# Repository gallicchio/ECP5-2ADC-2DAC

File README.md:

# ECP5-2ADC-2DAC

**Completely Open: Schematic, PCB, FPGA, Verilog, RISC-V processor, Linux, Ethernet, 2 ADCs, 2 DACs**

**Board A at work, 2026-11-18**, measuring the passive circuits on the AMOD-P board (left).
- **Cabling:** DAC 1 OUT drives a circuit and ADC A IN reads it back, over the SMA cables. The clock loops from CLK OUT back to CLK IN.
- **LEDs:** all eight red rail LEDs are lit, and so are a white user LED, the RGB LED (blue) and the Ethernet link LED (green).
- **Results:** every measurement so far is in [`bringup/BRINGUP_LOG.md`](bringup/BRINGUP_LOG.md).

> [!WARNING]
> ## Rev A mostly works, but only after soldering work. Wait for rev B.
> **Do not order this board yet.** Rev A's programming port is dead until two things are changed with a
> soldering iron and a cut cable, and it has other faults listed below. Rev B will fix them.

<p>  </p>

Rev A as delivered. The back is [here](photos/20261116_084538.jpg). The same board as drawn in KiCad:

<p>  </p>

Click any image to open it at full size.

## What it is for

A better version of the [Icepi Zero DAC/ADC tutorials](https://github.com/gallicchio/icepi-zero-dac-adc), on a
board made for them:

- **Two synchronized channels** in and two out, for things like I/Q. One dual ADC, one dual DAC.
- **Gigabit Ethernet**, so samples stream to a laptop at hundreds of megabits a second.
- **Nothing closed** between the laptop and the converters' pins. No vendor tool, no licence, no account.

| | |
|---|---|
| FPGA | Lattice ECP5, LFE5U-25F: 24k LUTs |
| Inputs | 2 x 12 bits, 65 MS/s (AD9238), DC-coupled, ±1 V, gain 1, 10 or 100, 50 Ω or high impedance |
| Outputs | 2 x 14 bits, 125 MS/s (AD9767), DC-coupled, ±1 V into 50 Ω |
| Clocks | 25 MHz TCXO, Si5351, clock in and clock out on SMA |
| Memory | 32 MB SDRAM, 16 MB flash, microSD |
| Ports | gigabit Ethernet, USB-C (JTAG and serial), a second USB-C, mini-HDMI, two Pmods |
| Extras | an LED driver and a photodiode receiver, for optics; a noise source |
| Board | 158 x 119 mm, 6 layers, one 5 V USB-C, about 3 W |

## Status of rev A

Two boards were assembled. One has been powered, on 2026-11-16 and 17.

| | status | detail |
|---|---|---|
| Power: every rail from one USB-C | **works** | |
| USB port for programming and serial | **dead as built** | works after the two changes below |
| Boot from flash | **works** | |
| 32 MB SDRAM | **works** | with its clock inverted in the FPGA; no error over the whole memory at 62.5 MHz |
| Clocks | **work** | the Si5351 to 225 MHz |
| ADC, both channels | **works** | clean to 87.5 MS/s; about 10.5 effective bits on small signals; large signals distort above about 2 MHz |
| DAC, both channels | **works** | clean at 187.5 MS/s |
| Gigabit Ethernet | **works** | both ADCs at 25 MS/s into GNU Radio: 858 Mbit/s, no packet lost |
| RISC-V Linux | **boots** | LiteX with a VexRiscv core at 50 MHz, Linux 6.12, loaded over the network |
| Second USB-C, the FPGA's own | does not work | cause not found |
| microSD | does not answer | not diagnosed |
| Pmod sockets | wrong | mirrored against the Pmod standard |
| HDMI, LED driver, photodiode receiver | not tested yet | |
| The second assembled board | not powered yet | |

The powered board's ADC stage was then damaged by a test lead that shorted on it. It still works; signals near
full scale are compressed. The record: [`bringup/STATUS.md`](bringup/STATUS.md),
[`bringup/BRINGUP_LOG.md`](bringup/BRINGUP_LOG.md).

### What rev A needs before it works

| fault | change |
|---|---|
| Two supply pins of the USB chip (FT2232H) get 1.8 V. They need 3.3 V. | Remove ferrite bead FB6241. Solder a wire from +3V3 to its **left pad only**. |
| The USB data lines D+ and D- are swapped at the chip. | Use a USB cable with those two wires crossed. |

Either fault alone keeps the board off the PC. A wire across both pads of FB6241 puts 3.3 V on the chip's 1.8 V
core. Every fault and its fix for rev B: [`bringup/REVB.md`](bringup/REVB.md).

## What "completely open" means here

| layer | what | built with |
|---|---|---|
| Schematic, PCB | a KiCad 10 project, generated by Python in `gen/` and `pcb/` | KiCad |
| FPGA | Lattice ECP5 | Yosys, nextpnr, Project Trellis, openFPGALoader |
| Verilog | the bring-up designs in [`gateware/bringup/`](gateware/bringup/README.md) | |
| RISC-V processor | VexRiscv in a LiteX system; the board's platform file is [`gateware/litex/`](gateware/litex/) | LiteX |
| Linux | 6.12, with a driver for the converters | Buildroot |
| Ethernet | RTL8211F PHY; UDP in Verilog, or LiteEth | |

The chips themselves are ordinary closed silicon with public data sheets.

Against a Red Pitaya STEMlab 125-14:

| | Red Pitaya | this board |
|---|---|---|
| Inputs | 2 x 14 bits, 125 MS/s | 2 x 12 bits, 65 MS/s |
| Outputs | 2 x 14 bits, 125 MS/s | 2 x 14 bits, 125 MS/s |
| FPGA and its tools | Xilinx Zynq: Vivado | Lattice ECP5: Yosys and nextpnr |
| Processor | ARM cores in the Zynq | a RISC-V core you can read, in the FPGA |
| Memory | 512 MB | 32 MB |

Fewer bits in and a slower processor; nothing you cannot open.

## What is here

| path | what |
|---|---|
| `*.kicad_sch`, `ECP5-2ADC-2DAC.kicad_pcb` | the KiCad 10 project; the schematic as [PDF](docs/images/ECP5-2ADC-2DAC_schematic.pdf) |
| [`mfg/release/`](mfg/release/) | what was uploaded to JLCPCB: Gerbers, BOM, placement |
| [`gateware/`](gateware/bringup/README.md) | the pin constraints, the bring-up Verilog and its bitstreams, the LiteX platform file |
| [`bringup/`](bringup/README.md) | the bench programs, the log of every measurement, the list for rev B |
| `gen/`, `pcb/`, `mfg/`, `tools/`, `sim/` | the scripts that generate and check the design (`python3 build.py`) |
| [`docs/DESIGN.md`](docs/DESIGN.md) | the design and its reasons, build by build |
| [`design_review/`](design_review/README.md) | six reviews before the order, and [what was done about them](DESIGN_REVIEW_RESPONSE.md) |
| [`photos/`](photos/README.md) | the board as delivered |

## How it was made

Jason Gallicchio designed this with Claude (Anthropic's Fable 5.1 and Opus 5.5, in Claude Code).

| | dates | days |
|---|---|---|
| Design, to the order at JLCPCB | 2026-10-01 to 2026-10-09 | 9 |
| Boards delivered | 2026-11-05 | |
| Bring-up and debugging so far | 2026-11-16 to 2026-11-17 | 2 |

Every prompt and every response is kept: [`CLAUDE_CODE_CHAT.md`](CLAUDE_CODE_CHAT.md).

The board grew up in a private repository of the research group. Its commits are here; vendor datasheets are
not. Commit hashes quoted in the documents are the old ones: [`docs/COMMIT_MAP.tsv`](docs/COMMIT_MAP.tsv).

## Licence

Hardware under CERN-OHL-P-2.0, software under MIT: [`LICENSE`](LICENSE).

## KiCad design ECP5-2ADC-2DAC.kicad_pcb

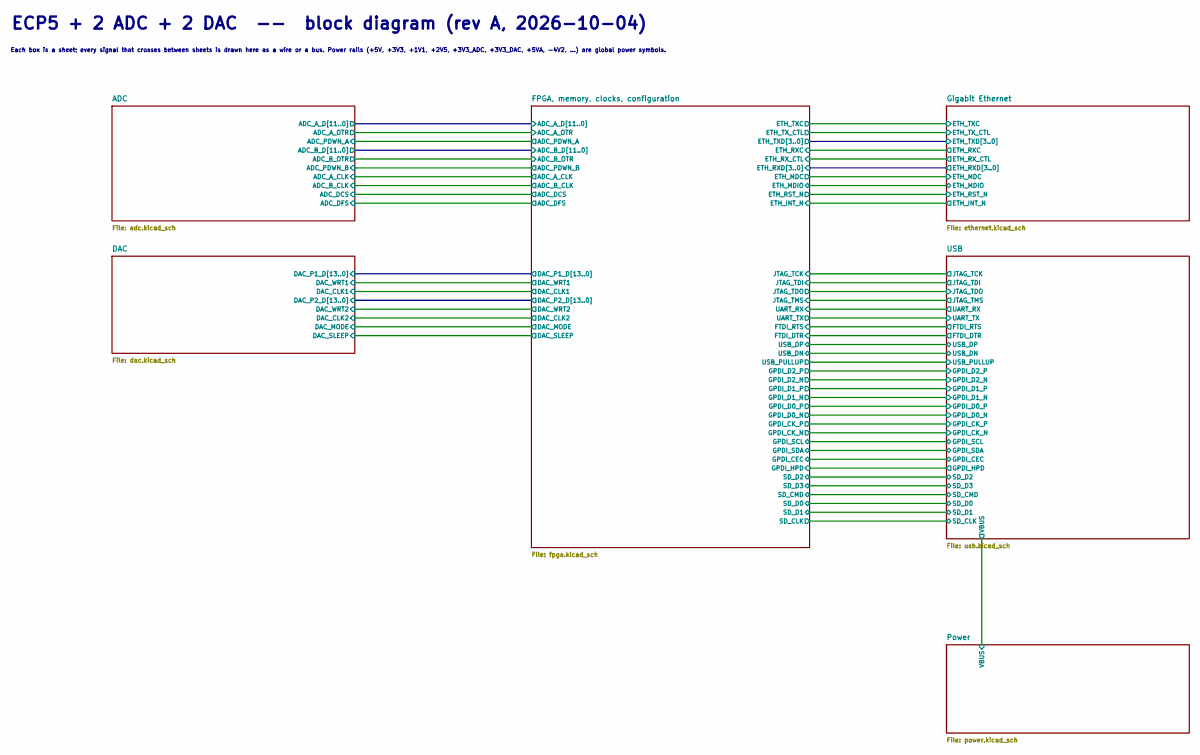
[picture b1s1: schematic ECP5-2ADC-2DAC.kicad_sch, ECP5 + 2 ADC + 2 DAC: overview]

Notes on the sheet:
ECP5 + 2 ADC + 2 DAC -- block diagram (rev A, 2026-10-04)
Each box is a sheet; every signal that crosses between sheets is drawn here as a wire or a bus. Power rails (+5V, +3V3, +1V1, +2V5, +3V3_ADC, +3V3_DAC, +5VA, -4V2, ...) are global power symbols.

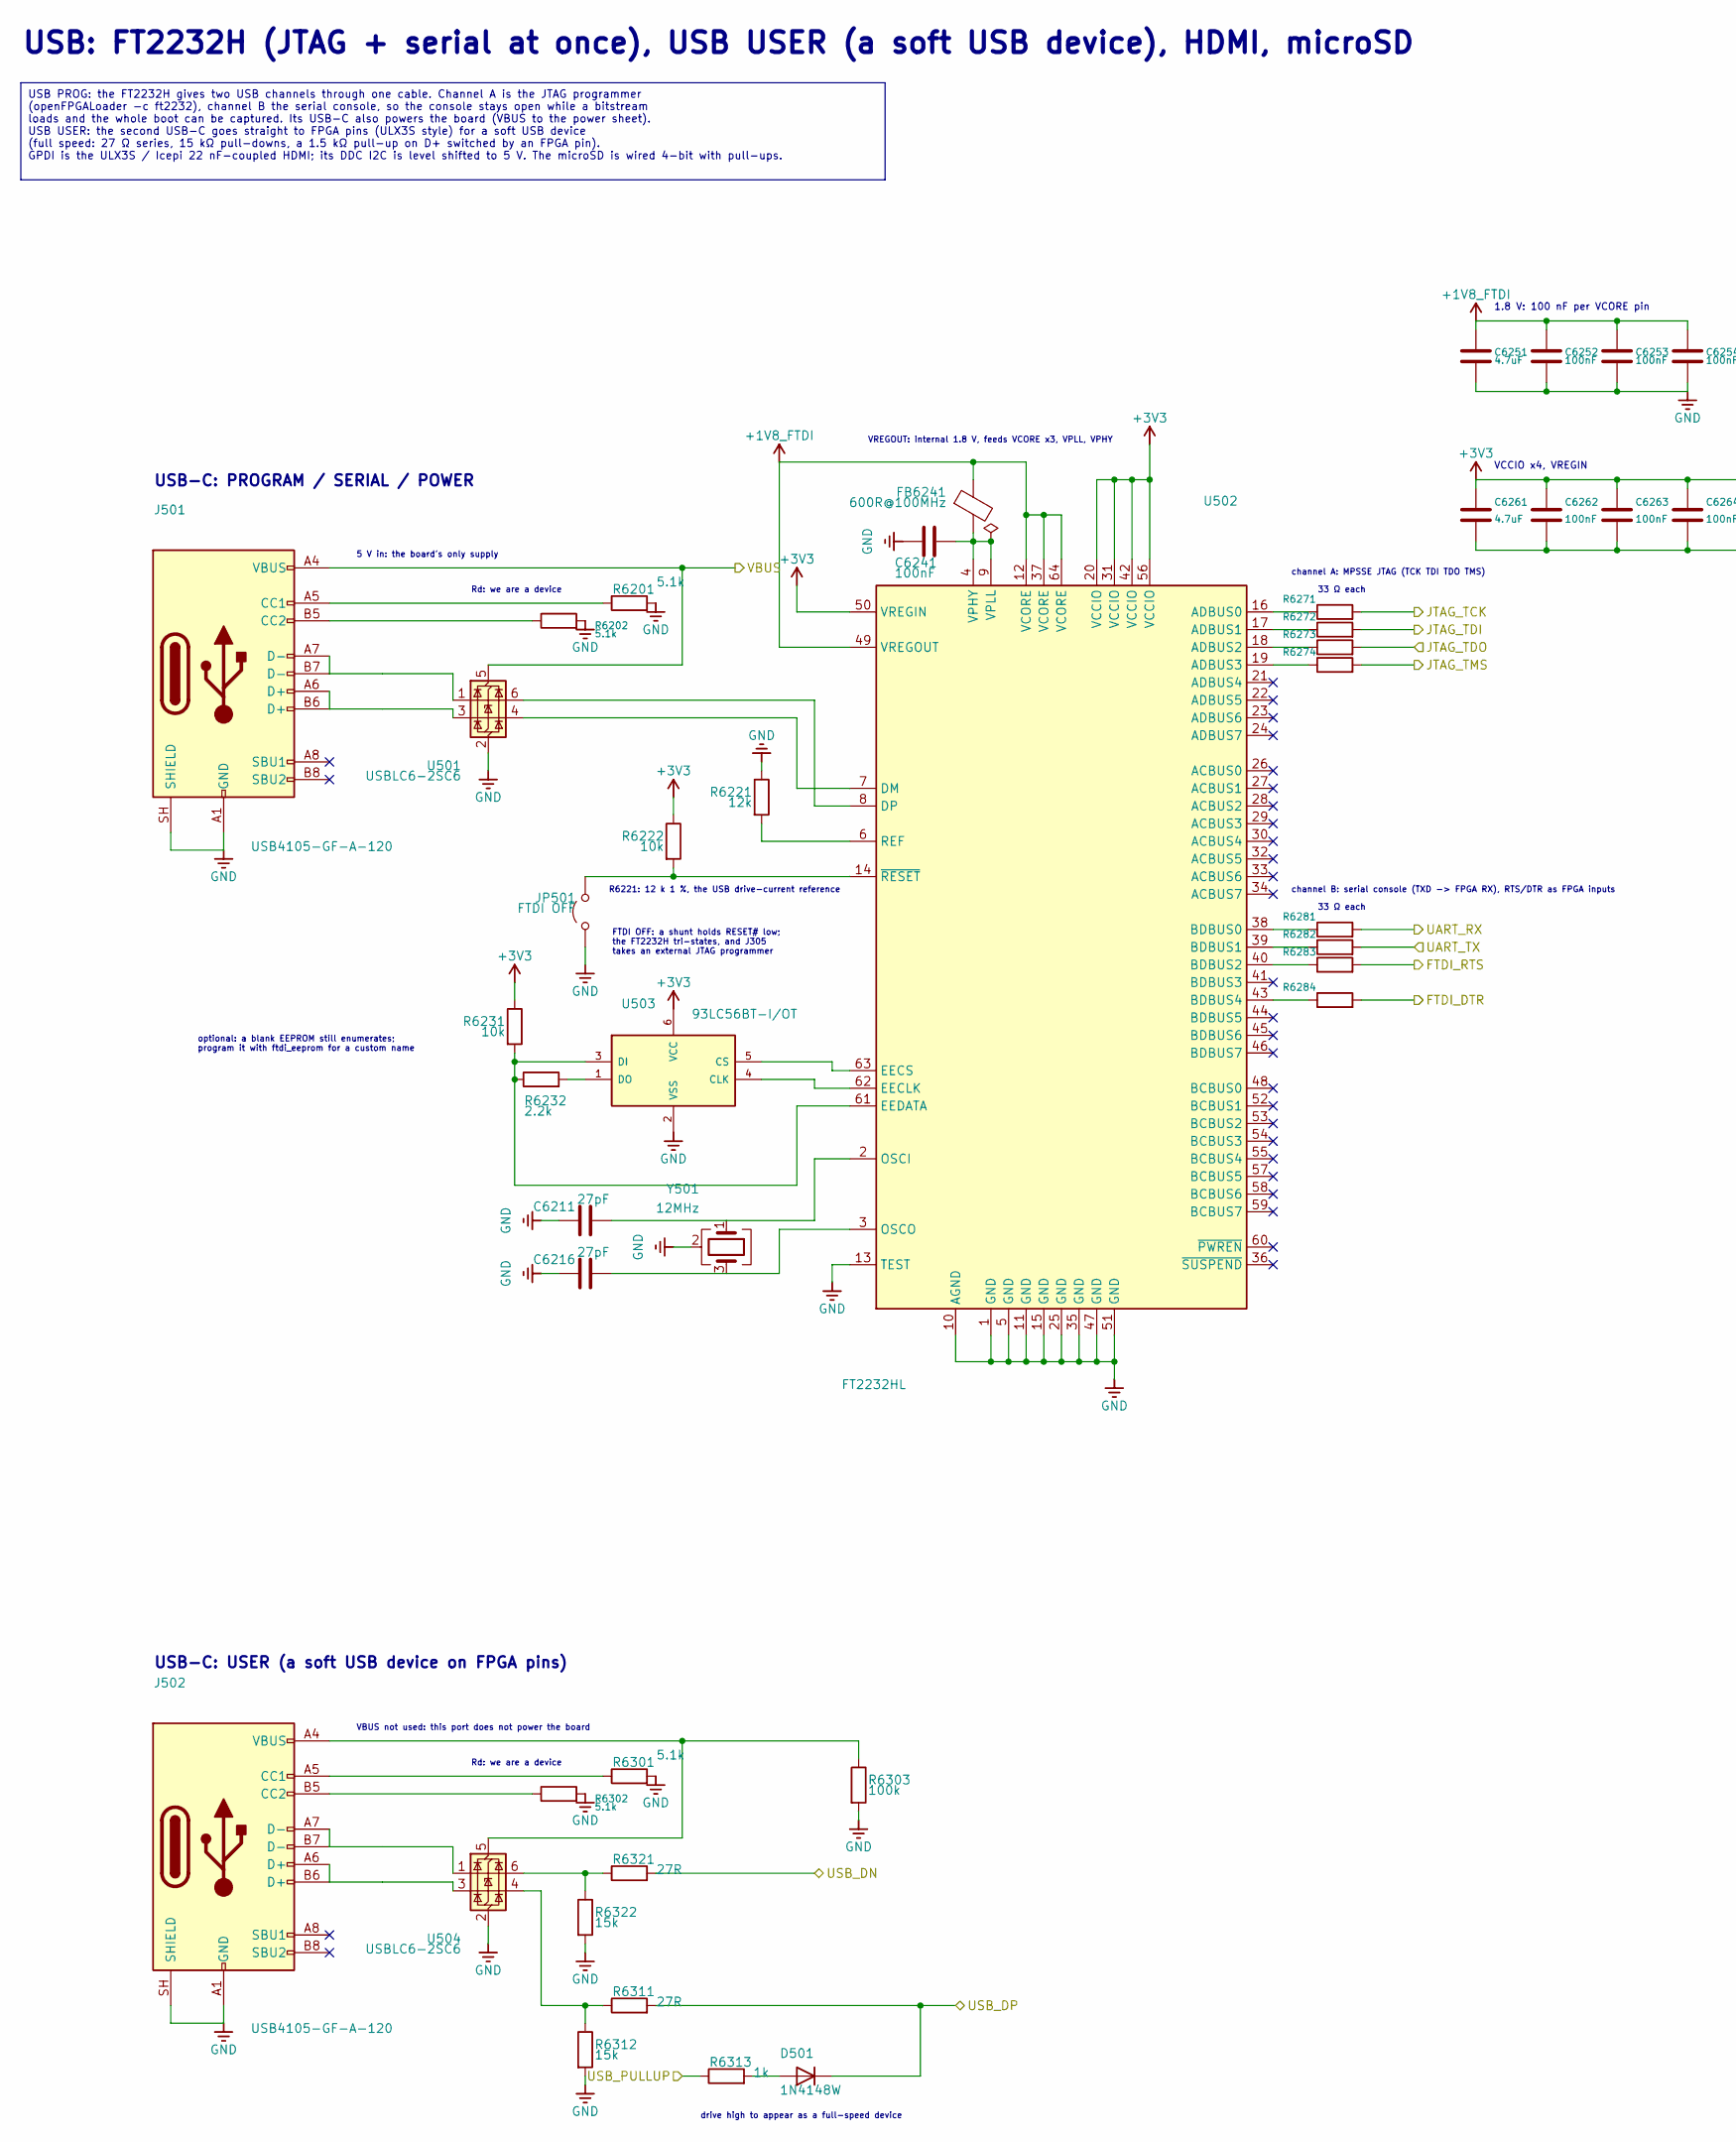
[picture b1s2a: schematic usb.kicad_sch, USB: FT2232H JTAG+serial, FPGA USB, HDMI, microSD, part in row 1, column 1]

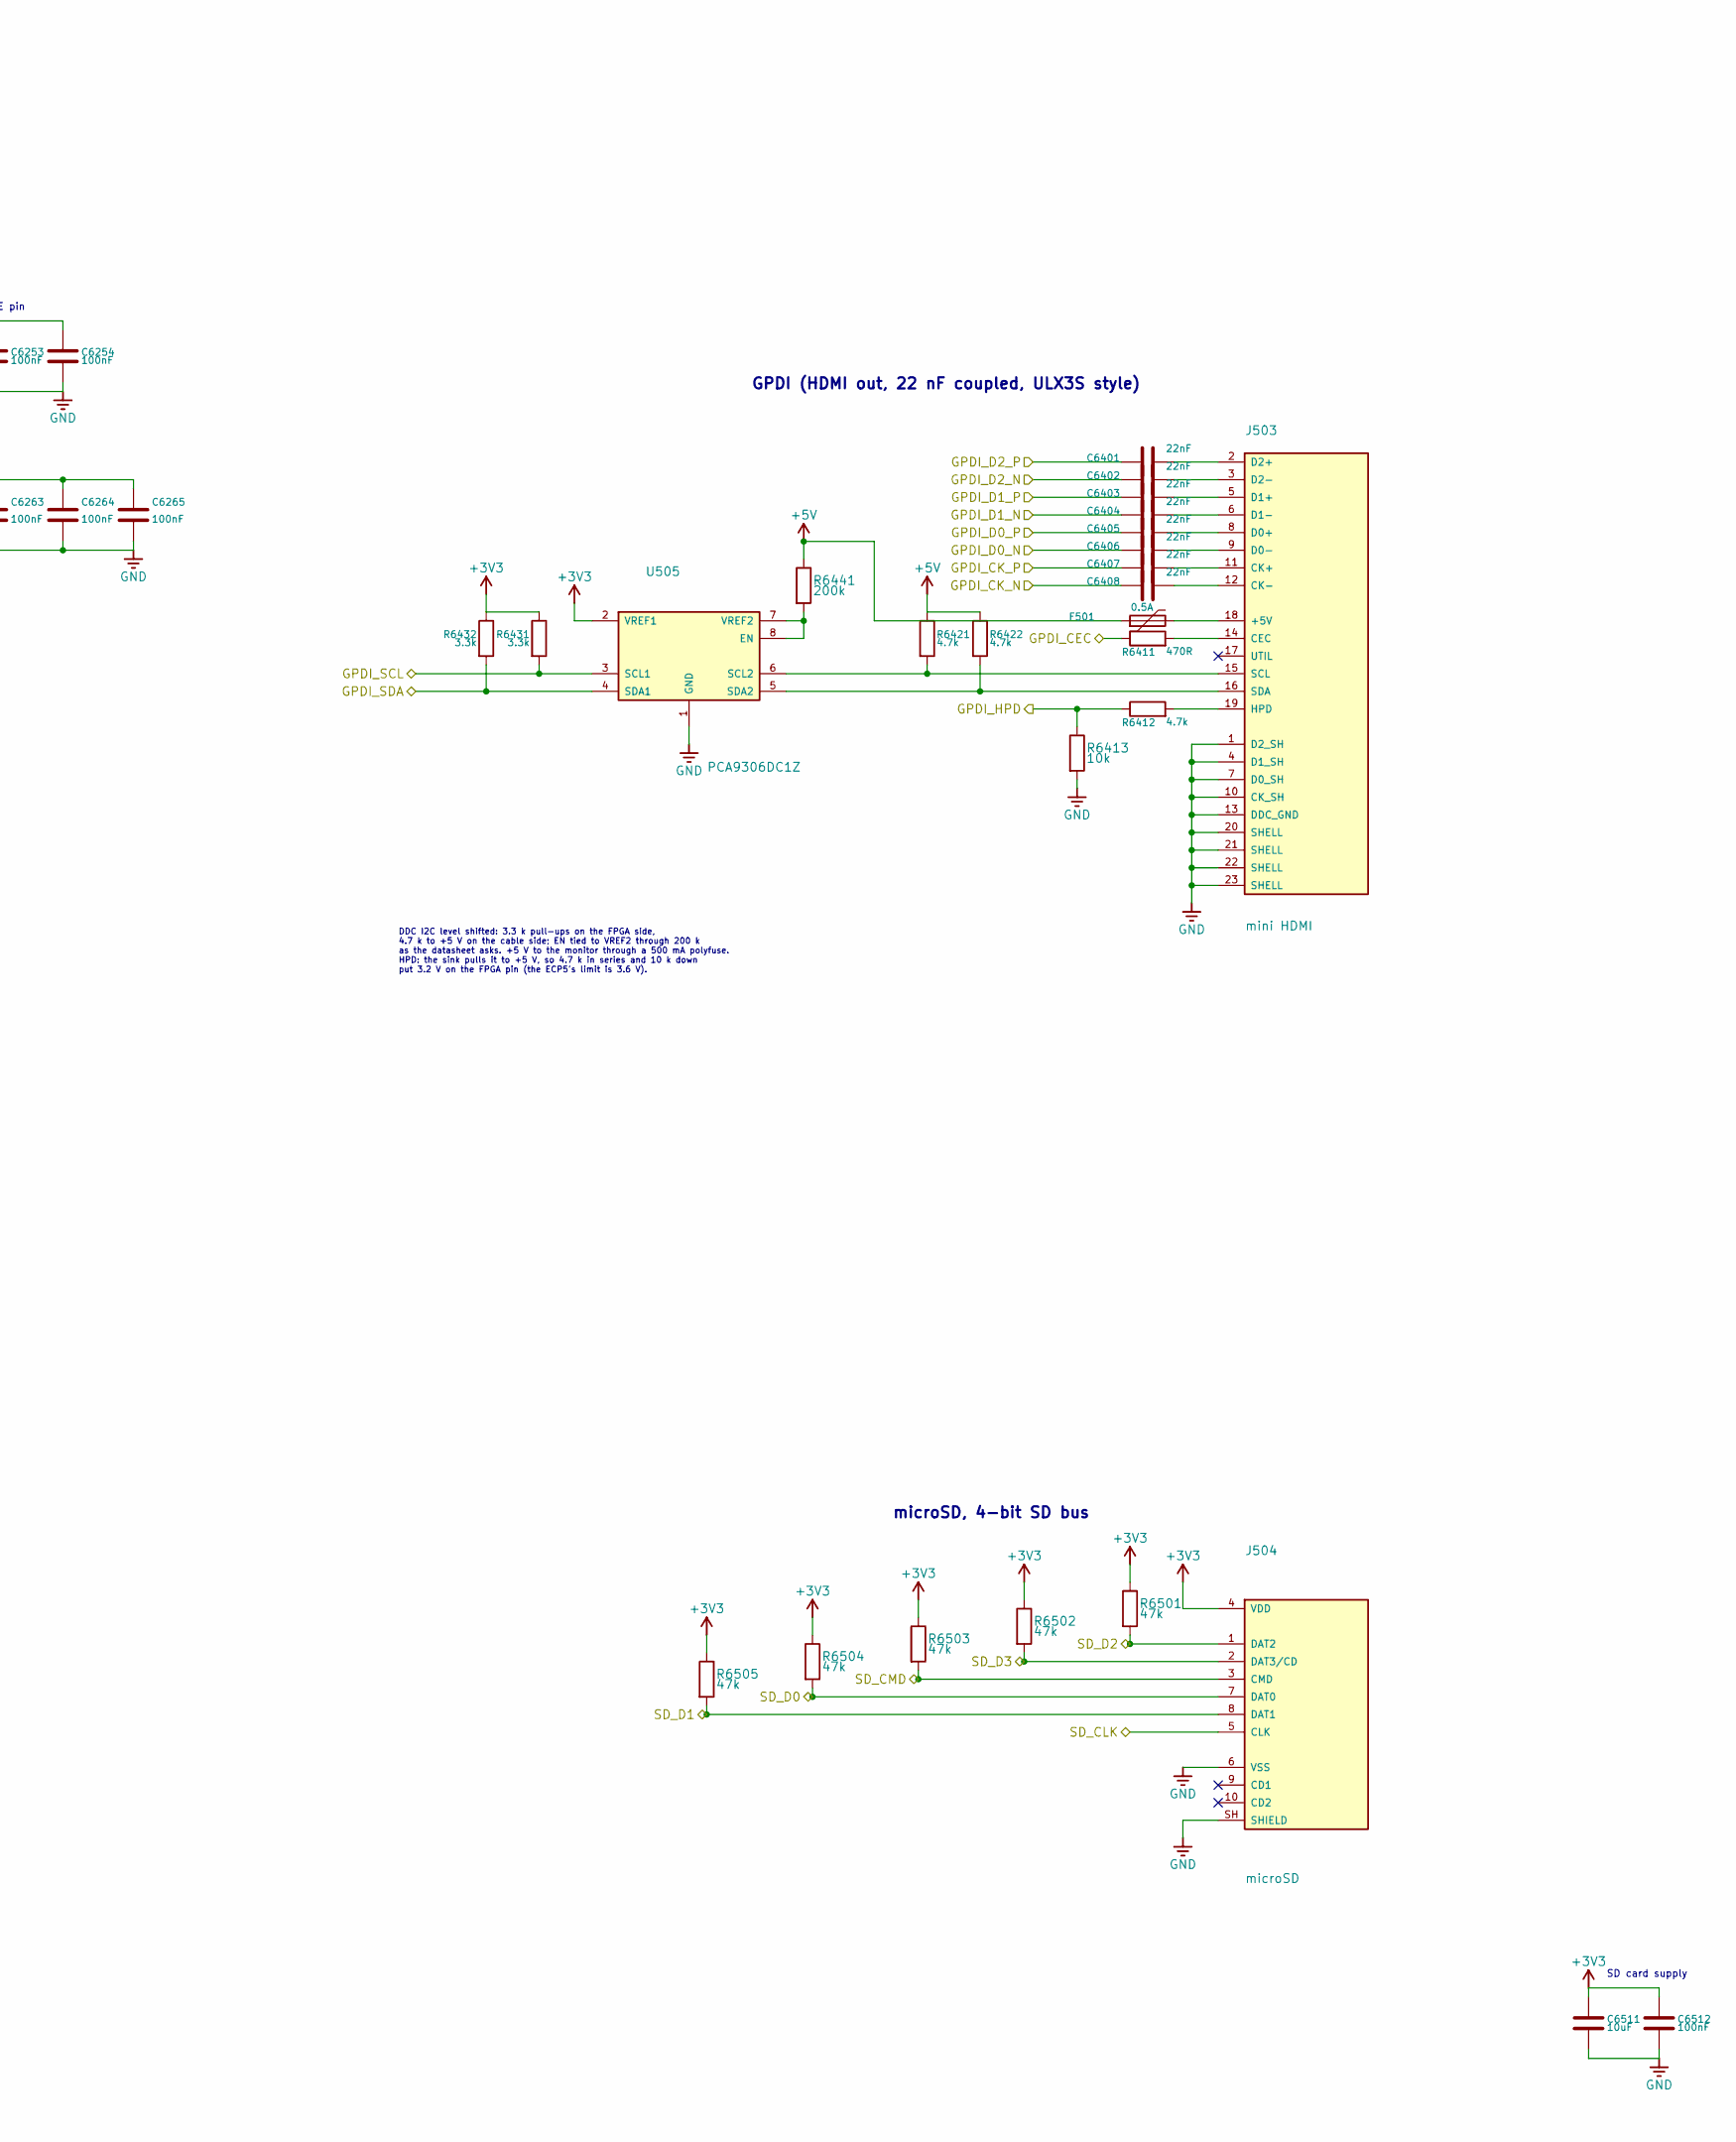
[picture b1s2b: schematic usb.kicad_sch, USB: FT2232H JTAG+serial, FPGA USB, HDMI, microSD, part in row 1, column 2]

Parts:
C6211, C6216: 27pF; C_0402_1005Metric; LCSC C1557
C6241, C6252, C6253, C6254, C6262, C6263, C6264, C6265, C6512: 100nF; C_0402_1005Metric; LCSC C1525
C6251, C6261: 4.7uF; C_0603_1608Metric; LCSC C19666
C6401, C6402, C6403, C6404, C6405, C6406, C6407, C6408: 22nF; C_0402_1005Metric; LCSC C1532
C6511: 10uF; C_0603_1608Metric; LCSC C96446
D501: 1N4148W; D_SOD-123; LCSC C81598
F501: 0.5A; Fuse_1812_4532Metric; LCSC C17313
FB6241: 600R@100MHz; L_0603_1608Metric; LCSC C85833
J501, J502: USB4105-GF-A-120; USB_C_Receptacle_GCT_USB4105-xx-A_16P_TopMnt_Horizontal; LCSC C5184243
J503: mini HDMI; HDMI-SMD_A71-05H4-111N1; LCSC C2682170
J504: microSD; TF-SMD_TF-01A; LCSC C91145
JP501: FTDI OFF; PinHeader_1x02_P2.54mm_Vertical; LCSC C2337
R6201, R6202, R6301, R6302: 5.1k; R_0603_1608Metric; LCSC C23186
R6221: 12k; R_0603_1608Metric; LCSC C22790
R6222, R6231, R6413: 10k; R_0603_1608Metric; LCSC C25804
R6232: 2.2k; R_0603_1608Metric; LCSC C4190
R6271, R6272, R6273, R6274, R6281, R6282, R6283, R6284: 33R; R_0603_1608Metric; LCSC C23140
R6303: 100k; R_0603_1608Metric; LCSC C25803
R6311, R6321: 27R; R_0603_1608Metric; LCSC C25190
R6312, R6322: 15k; R_0603_1608Metric; LCSC C22809
R6313: 1k; R_0603_1608Metric; LCSC C21190
R6411: 470R; R_0603_1608Metric; LCSC C23179
R6412, R6421, R6422: 4.7k; R_0603_1608Metric; LCSC C23162
R6431, R6432: 3.3k; R_0603_1608Metric; LCSC C22978
R6441: 200k; R_0603_1608Metric; LCSC C25811
R6501, R6502, R6503, R6504, R6505: 47k; R_0603_1608Metric; LCSC C25819
U501, U504: USBLC6-2SC6; SOT-23-6; LCSC C2827654
U502: FT2232HL; LQFP-64_10x10mm_P0.5mm; LCSC C27882
U503: 93LC56BT-I/OT; SOT-23-6; LCSC C190271
U505: PCA9306DC1Z; VSSOP-8_2.3x2mm_P0.5mm; LCSC C5119911
Y501: 12MHz; Crystal_SMD_3225-4Pin_3.2x2.5mm; LCSC C9002

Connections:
+1V8_FTDI: C6251.1, C6252.1, C6253.1, C6254.1, FB6241.1, U502.12 (VCORE), U502.37 (VCORE), U502.49 (VREGOUT), U502.64 (VCORE)
+3V3: C6261.1, C6262.1, C6263.1, C6264.1, C6265.1, C6511.1, C6512.1, J504.4 (VDD), R6222.1, R6231.1, R6431.1, R6432.1, R6501.1, R6502.1, R6503.1, R6504.1, R6505.1, U502.20 (VCCIO), U502.31 (VCCIO), U502.42 (VCCIO), U502.50 (VREGIN), U502.56 (VCCIO), U503.6 (VCC), U505.2 (VREF1); also elsewhere on the board
+5V: F501.1, R6421.1, R6422.1, R6441.1; also elsewhere on the board
/FPGA, memory, clocks, configuration/FTDI_DTR: R6284.2; also elsewhere on the board
/FPGA, memory, clocks, configuration/FTDI_RTS: R6283.2; also elsewhere on the board
/FPGA, memory, clocks, configuration/GPDI_CEC: R6411.1; also elsewhere on the board
/FPGA, memory, clocks, configuration/GPDI_CK_N: C6408.1; also elsewhere on the board
/FPGA, memory, clocks, configuration/GPDI_CK_P: C6407.1; also elsewhere on the board
/FPGA, memory, clocks, configuration/GPDI_D0_N: C6406.1; also elsewhere on the board
/FPGA, memory, clocks, configuration/GPDI_D0_P: C6405.1; also elsewhere on the board
/FPGA, memory, clocks, configuration/GPDI_D1_N: C6404.1; also elsewhere on the board
/FPGA, memory, clocks, configuration/GPDI_D1_P: C6403.1; also elsewhere on the board
/FPGA, memory, clocks, configuration/GPDI_D2_N: C6402.1; also elsewhere on the board
/FPGA, memory, clocks, configuration/GPDI_D2_P: C6401.1; also elsewhere on the board
/FPGA, memory, clocks, configuration/GPDI_HPD: R6412.1, R6413.1; also elsewhere on the board
/FPGA, memory, clocks, configuration/GPDI_SCL: R6431.2, U505.3 (SCL1); also elsewhere on the board
/FPGA, memory, clocks, configuration/GPDI_SDA: R6432.2, U505.4 (SDA1); also elsewhere on the board
/FPGA, memory, clocks, configuration/JTAG_TCK: R6271.2; also elsewhere on the board
/FPGA, memory, clocks, configuration/JTAG_TDI: R6272.2; also elsewhere on the board
/FPGA, memory, clocks, configuration/JTAG_TDO: R6273.2; also elsewhere on the board
/FPGA, memory, clocks, configuration/JTAG_TMS: R6274.2; also elsewhere on the board
/FPGA, memory, clocks, configuration/SD_CLK: J504.5 (CLK); also elsewhere on the board
/FPGA, memory, clocks, configuration/SD_CMD: J504.3 (CMD), R6503.2; also elsewhere on the board
/FPGA, memory, clocks, configuration/SD_D0: J504.7 (DAT0), R6504.2; also elsewhere on the board
/FPGA, memory, clocks, configuration/SD_D1: J504.8 (DAT1), R6505.2; also elsewhere on the board
/FPGA, memory, clocks, configuration/SD_D2: J504.1 (DAT2), R6501.2; also elsewhere on the board
/FPGA, memory, clocks, configuration/SD_D3: J504.2 (DAT3/CD), R6502.2; also elsewhere on the board
/FPGA, memory, clocks, configuration/UART_RX: R6281.2; also elsewhere on the board
/FPGA, memory, clocks, configuration/UART_TX: R6282.2; also elsewhere on the board
/FPGA, memory, clocks, configuration/USB_DN: R6321.2; also elsewhere on the board
/FPGA, memory, clocks, configuration/USB_DP: D501.1 (K), R6311.2; also elsewhere on the board
/FPGA, memory, clocks, configuration/USB_PULLUP: R6313.1; also elsewhere on the board
/Power/VBUS: J501.A4 (VBUS), J501.A9 (VBUS), J501.B4 (VBUS), J501.B9 (VBUS), U501.5 (VBUS); also elsewhere on the board
GND: C6211.1, C6216.1, C6241.1, C6251.2, C6252.2, C6253.2, C6254.2, C6261.2, C6262.2, C6263.2, C6264.2, C6265.2, C6511.2, C6512.2, J501.A1 (GND), J501.A12 (GND), J501.B1 (GND), J501.B12 (GND), J501.SH (SHIELD), J502.A1 (GND), J502.A12 (GND), J502.B1 (GND), J502.B12 (GND), J502.SH (SHIELD), J503.1 (D2_SH), J503.4 (D1_SH), J503.7 (D0_SH), J503.10 (CK_SH), J503.13 (DDC_GND), J503.20 (SHELL), J503.21 (SHELL), J503.22 (SHELL), J503.23 (SHELL), J504.6 (VSS), J504.SH (SHIELD), JP501.1 (A), R6201.2, R6202.2, R6221.1, R6301.2, R6302.2, R6303.2, R6312.2, R6322.2, R6413.2, U501.2 (GND), U502.1 (GND), U502.5 (GND), U502.10 (AGND), U502.11 (GND), U502.13 (TEST), U502.15 (GND), U502.25 (GND), U502.35 (GND), U502.47 (GND), U502.51 (GND), U503.2 (VSS), U504.2 (GND), U505.1 (GND), Y501.2 (G), Y501.4 (G); also elsewhere on the board
unnamed: D501.2 (A), R6313.2
unnamed: J501.A5 (CC1), R6201.1
unnamed: J501.B5 (CC2), R6202.1
unnamed: J501.A6 (D+), J501.B6 (D+), U501.3 (I/O2)
unnamed: J501.A7 (D-), J501.B7 (D-), U501.1 (I/O1)
unnamed: J502.A5 (CC1), R6301.1
unnamed: J502.B5 (CC2), R6302.1
unnamed: J502.A6 (D+), J502.B6 (D+), U504.3 (I/O2)
unnamed: J502.A7 (D-), J502.B7 (D-), U504.1 (I/O1)
unnamed: F501.2, J503.18 (+5V)
unnamed: J503.14 (CEC), R6411.2
unnamed: C6407.2, J503.11 (CK+)
unnamed: C6408.2, J503.12 (CK-)
unnamed: C6405.2, J503.8 (D0+)
unnamed: C6406.2, J503.9 (D0-)
unnamed: C6403.2, J503.5 (D1+)
unnamed: C6404.2, J503.6 (D1-)
unnamed: C6401.2, J503.2 (D2+)
unnamed: C6402.2, J503.3 (D2-)
unnamed: J503.19 (HPD), R6412.2
unnamed: J503.15 (SCL), R6421.2, U505.6 (SCL2)
unnamed: J503.16 (SDA), R6422.2, U505.5 (SDA2)
unnamed: JP501.2 (B), R6222.2, U502.14 (~RESET)
unnamed: R6311.1, R6312.1, U504.4 (I/O2)
unnamed: R6321.1, R6322.1, U504.6 (I/O1)
unnamed: R6271.1, U502.16 (ADBUS0)
unnamed: R6272.1, U502.17 (ADBUS1)
unnamed: R6273.1, U502.18 (ADBUS2)
unnamed: R6274.1, U502.19 (ADBUS3)
unnamed: R6281.1, U502.38 (BDBUS0)
unnamed: R6282.1, U502.39 (BDBUS1)
unnamed: R6283.1, U502.40 (BDBUS2)
unnamed: R6284.1, U502.43 (BDBUS4)
unnamed: U501.4 (I/O2), U502.7 (DM)
unnamed: U501.6 (I/O1), U502.8 (DP)
unnamed: U502.62 (EECLK), U503.4 (CLK)
unnamed: U502.63 (EECS), U503.5 (CS)
unnamed: R6231.2, R6232.1, U502.61 (EEDATA), U503.3 (DI)
unnamed: C6211.2, U502.2 (OSCI), Y501.1
unnamed: C6216.2, U502.3 (OSCO), Y501.3
unnamed: R6221.2, U502.6 (REF)
unnamed: C6241.2, FB6241.2, U502.4 (VPHY), U502.9 (VPLL)
unnamed: R6232.2, U503.1 (DO)
unnamed: J502.A4 (VBUS), J502.A9 (VBUS), J502.B4 (VBUS), J502.B9 (VBUS), R6303.1, U504.5 (VBUS)
unnamed: R6441.2, U505.7 (VREF2), U505.8 (EN)

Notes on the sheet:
channel A: MPSSE JTAG (TCK TDI TDO TMS)
channel B: serial console (TXD -> FPGA RX), RTS/DTR as FPGA inputs
USB-C: USER (a soft USB device on FPGA pins)
USB: FT2232H (JTAG + serial at once), USB USER (a soft USB device), HDMI, microSD
optional: a blank EEPROM still enumerates; program it with ftdi_eeprom for a custom name
33 Ω each
Rd: we are a device
VBUS not used: this port does not power the board
VREGOUT: internal 1.8 V, feeds VCORE x3, VPLL, VPHY
microSD, 4-bit SD bus
VCCIO x4, VREGIN
FTDI OFF: a shunt holds RESET# low; the FT2232H tri-states, and J305 takes an external JTAG programmer
R6221: 12 k 1 %, the USB drive-current reference
DDC I2C level shifted: 3.3 k pull-ups on the FPGA side, 4.7 k to +5 V on the cable side; EN tied to VREF2 through 200 k as the datasheet asks. +5 V to the monitor through a 500 mA polyfuse. HPD: the sink pulls it to +5 V, so 4.7 k in series and 10 k down put 3.2 V on the FPGA pin (the ECP5's limit 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
1.8 V: 100 nF per VCORE pin
USB-C: PROGRAM / SERIAL / POWER
5 V in: the board's only supply
drive high to appear as a full-speed device
GPDI (HDMI out, 22 nF coupled, ULX3S style)
SD card supply
USB PROG: the FT2232H gives two USB channels through one cable. Channel A is the JTAG programmer (openFPGALoader -c ft2232), channel B the serial console, so the console stays open while a bitstream loads and the whole boot can be captured. Its USB-C also powers the board (VBUS to the power sheet).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
